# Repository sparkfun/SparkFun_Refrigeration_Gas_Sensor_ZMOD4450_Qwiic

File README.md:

SparkX Refrigeration Gas Sensor - ZMOD4450 (Qwiic)
========================================

[*SparkX Refrigeration Gas Sensor - ZMOD4450 (Qwiic) (SPX-16677)*](https://www.sparkfun.com/products/16677)

The ZMOD4450 from Renesas is a refrigeration air quality sensor designed to measure gases typically emitted during food ripening and rotting. The sensor measures ethlyene, amines and volatile sulfur compounds and reports the data via I<sup>2</sup>C. This breakout from SparkX uses the Qwiic system to easily add this sensor into your Qwiic chain. 

Feel like supporting open-source hardware? Buy a [board](https://www.sparkfun.com/products/16677) from SparkFun!

Repository Contents
-------------------

* **/Documentation** - Data sheets, additional product information
* **/Firmware** - Target Specific I<sup>2</sup>C and Low Level Functions
* **/Hardware** - Eagle design files (.brd, .sch)
* **/Production** - Production panel files (.brd)

Product Versions
----------------
* [SPX-16677](https://www.sparkfun.com/products/16677)- Original SparkX release of the Refrigeration Gas Sensor - ZMOD4450

License Information
-------------------

This product is _**open source**_! 

Please review the LICENSE.md file for license information. 

If you have any questions or concerns on licensing, please contact technical support on our [SparkFun forums](https://forum.sparkfun.com/viewforum.php?f=152).

Distributed as-is; no warranty is given.

- Your friends at SparkFun.

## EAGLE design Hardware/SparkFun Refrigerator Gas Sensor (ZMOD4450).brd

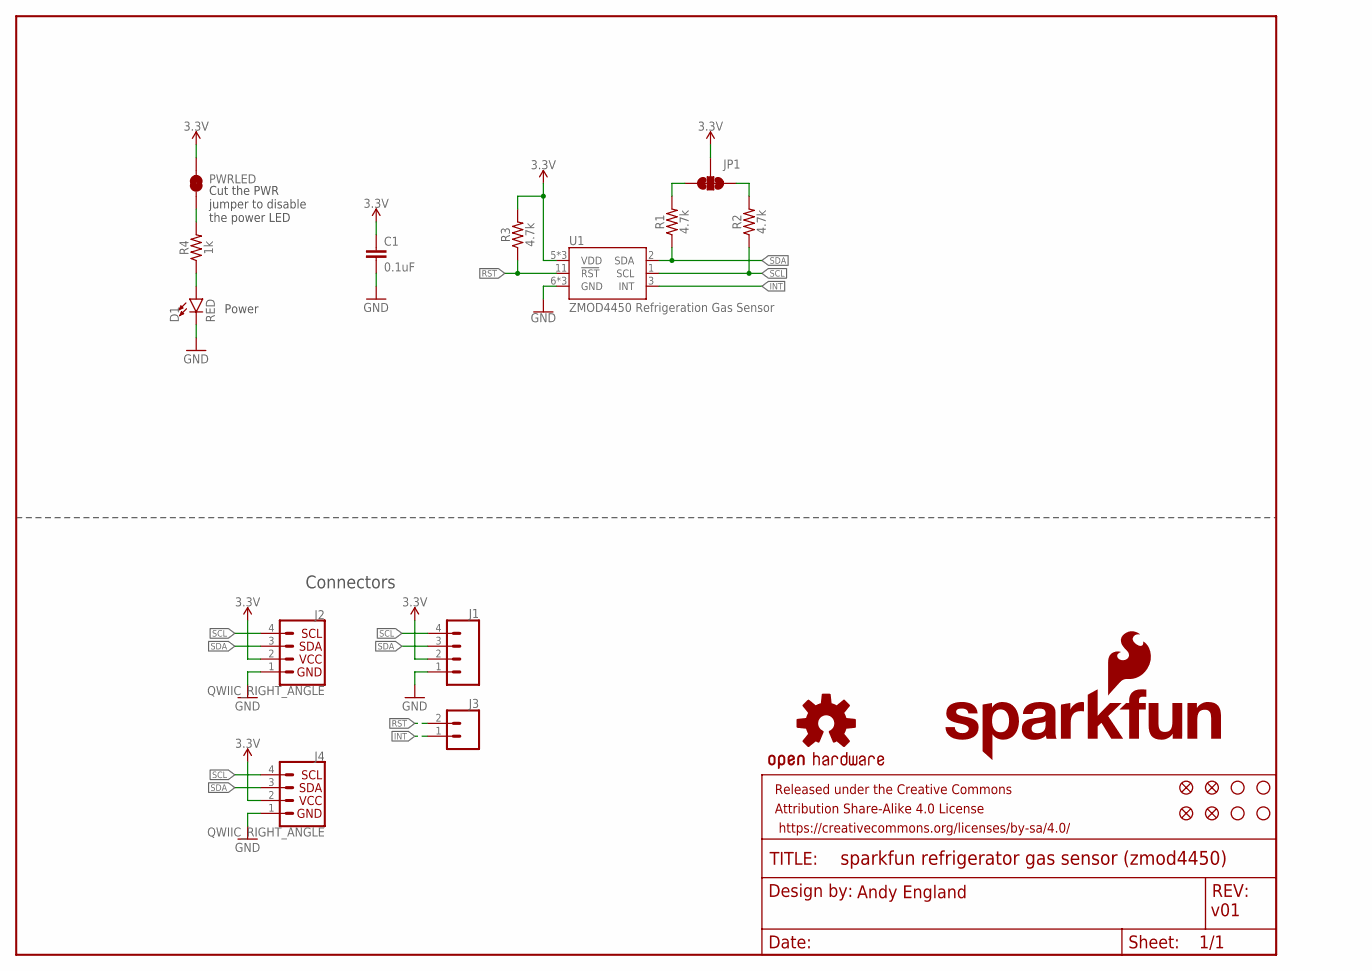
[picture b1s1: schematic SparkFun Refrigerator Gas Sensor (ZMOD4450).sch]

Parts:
C1: 0.1uF; 0603
D1: RED; LED-0603
FD1, FD2, FD3, FD4: FIDUCIALUFIDUCIAL; FIDUCIAL-MICRO
FRAME1: FRAME-LETTER; CREATIVE_COMMONS
H1, H2, H3, H4: STAND-OFF
J1: CONN_041X04_NO_SILK; 1X04_NO_SILK
J2, J4: QWIIC_RIGHT_ANGLE; JST04_1MM_RA
J3: CONN_021X02_NO_SILK; 1X02_NO_SILK
JP1: JUMPER-SMT_3_2-NC_TRACE_SILK; SMT-JUMPER_3_2-NC_TRACE_SILK
LOGO1: OSHW-LOGOS; OSHW-LOGO-S
LOGO2: SFE_LOGO_NAME_FLAME.1_INCH; SFE_LOGO_NAME_FLAME_.1
PWRLED: JUMPER-SMT_2_NC_TRACE_SILK; SMT-JUMPER_2_NC_TRACE_SILK
R1, R2, R3: 4.7k; 0603@1
R4: 1k; 0603
U1: ZMOD4450 Refrigeration Gas Sensor; LGA-12-3X3

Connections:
3.3V: C1.1, J1.2, J2.2, J4.2, JP1.2, PWRLED.2, R3.2, U1.5 (VDD), U1.10 (VDD), U1.12 (VDD); also elsewhere on the board
!RST: J3.2, R3.1, U1.11 (!RST)
GND: C1.2, D1.C, J1.1, J2.1, J4.1, U1.6 (GND), U1.7 (GND), U1.9 (GND)
INT: J3.1, U1.3 (INT)
unnamed 4: JP1.3, R1.2; also elsewhere on the board
unnamed: D1.A, R4.1
unnamed 6: JP1.1, R2.2; also elsewhere on the board
unnamed: PWRLED.1, R4.2
SCL: J1.4, J2.4, J4.4, R2.1, U1.1 (SCL)
SDA: J1.3, J2.3, J4.3, R1.1, U1.2 (SDA)

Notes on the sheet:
Andy England
v01
Power
Connectors
Cut the PWR jumper to disable the power LED

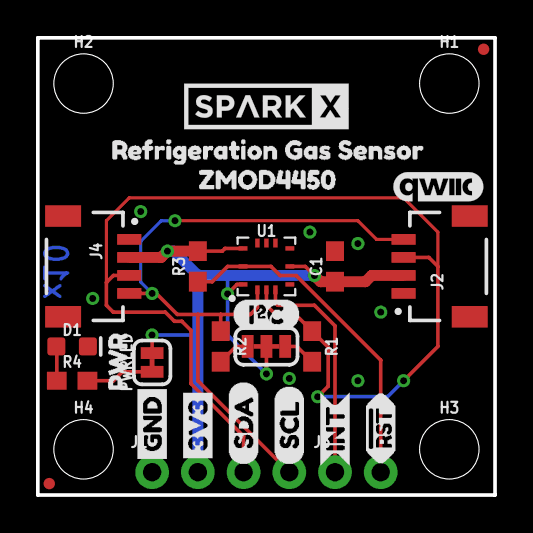
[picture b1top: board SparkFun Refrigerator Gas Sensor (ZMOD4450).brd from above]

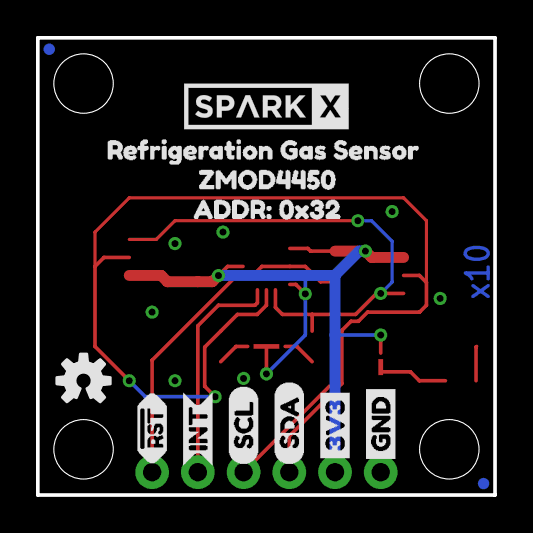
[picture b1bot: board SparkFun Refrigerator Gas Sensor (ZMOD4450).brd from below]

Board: 2 copper layers, 25.4 x 25.4 mm, 46 parts (13 on the bottom side), 10 nets.

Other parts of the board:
I2C: JUMPER-SMT_3_2-NC_TRACE_SILK; SMT-JUMPER_3_2-NC_TRACE_SILK
U$1, U$2: GND_P
U$3, U$20: ZMOD44501
U$4, U$14: INT_O
U$5, U$6: 3V3_P
U$7, U$8: SDA_IO
U$9, U$10: SCL_IO
U$11: I2C
U$12: PWR_TO
U$13, U$16: !RST_I
U$15, U$17: REFRIGERATION_GAS_SENSOR0
U$18, U$19: SPARKX-MEDIUM
U$21: ADDR#_0X320
U$22: PRODUCTION_INSTRUCTIONS

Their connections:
3.3V: I2C.2; also elsewhere on the board
unnamed 4: I2C.3; also elsewhere on the board
unnamed 6: I2C.1; also elsewhere on the board

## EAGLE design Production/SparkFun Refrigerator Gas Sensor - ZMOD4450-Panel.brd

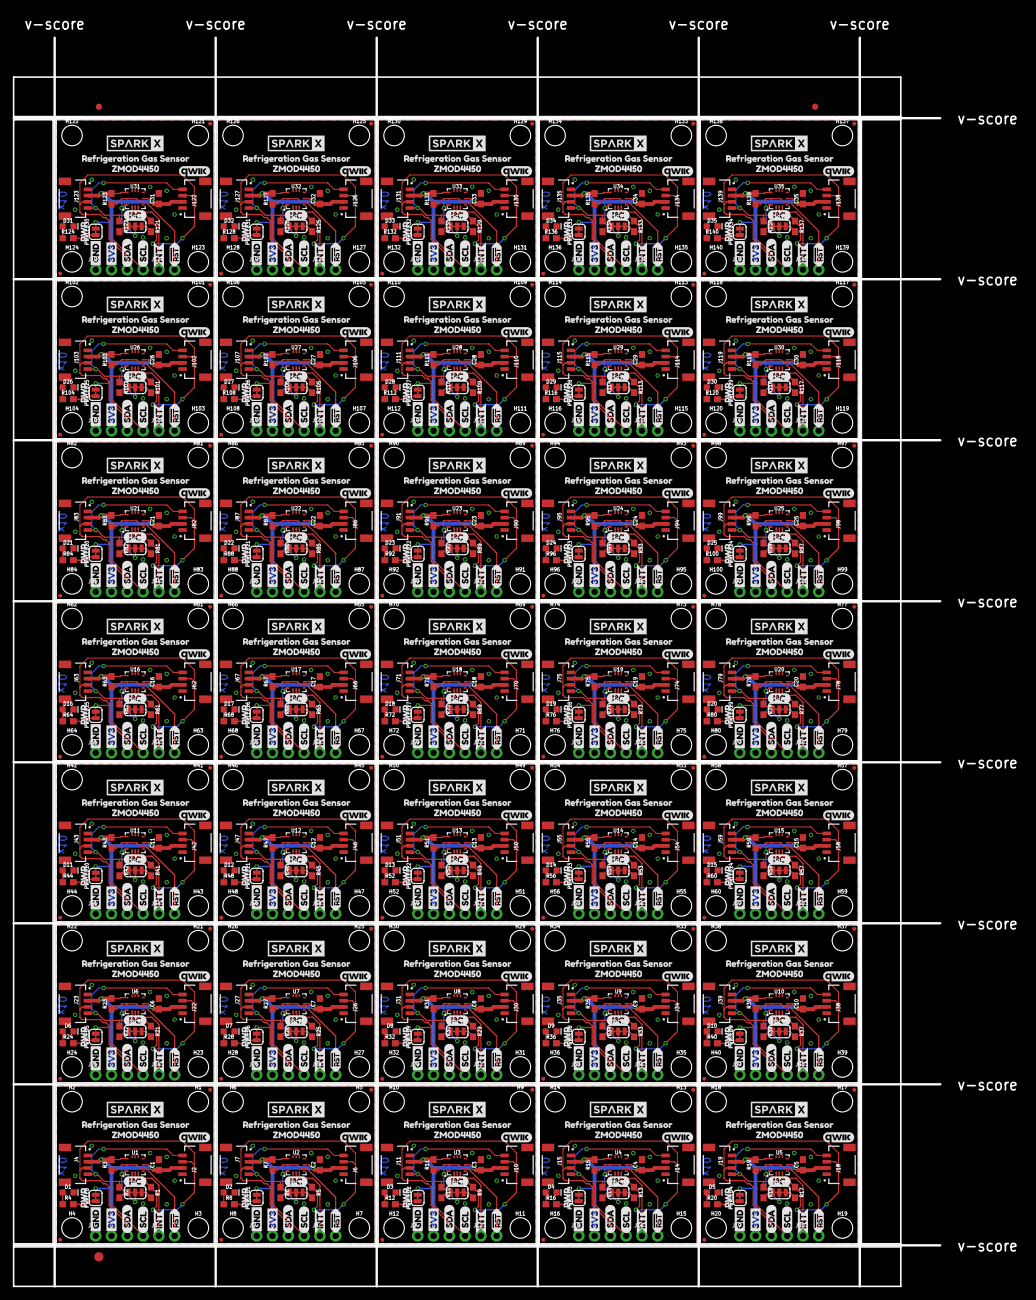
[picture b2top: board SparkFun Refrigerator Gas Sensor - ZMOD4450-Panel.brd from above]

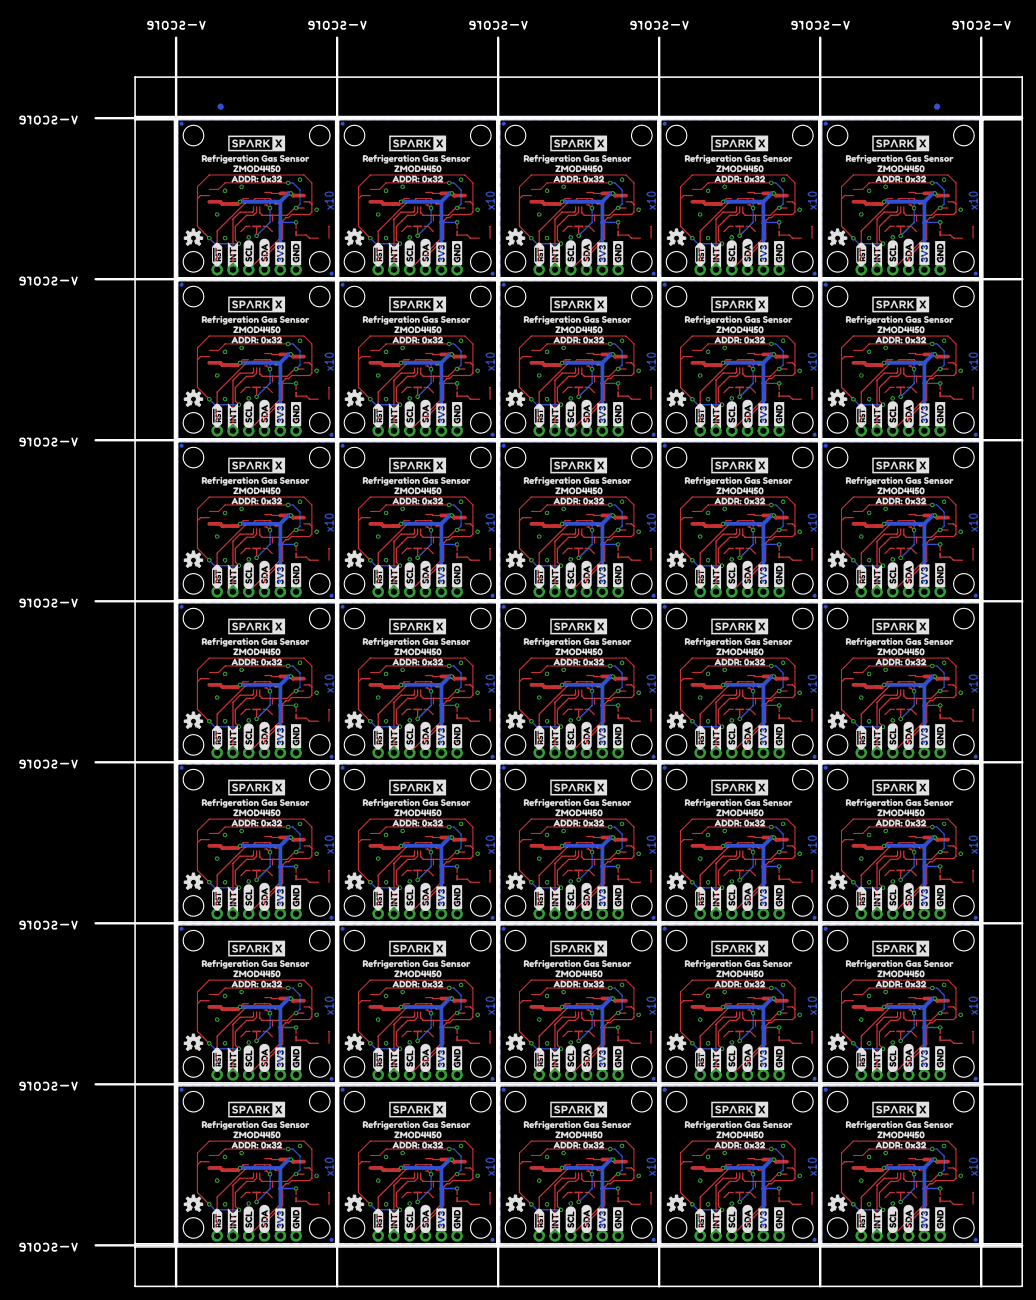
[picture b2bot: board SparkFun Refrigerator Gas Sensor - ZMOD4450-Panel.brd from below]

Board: 2 copper layers, 162.3 x 204.8 mm, 1615 parts (457 on the bottom side), 350 nets.

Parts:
C1, C2, C3, C4, C5, C6, C7, C8, C9, C10, C11, C12, C13, C14, C15, C16, C17, C18, C19, C20, C21, C22, C23, C24, C25, C26, C27, C28, C29, C30, C31, C32, C33, C34, C35: 0.1uF; 0603
D1, D2, D3, D4, D5, D6, D7, D8, D9, D10, D11, D12, D13, D14, D15, D16, D17, D18, D19, D20, D21, D22, D23, D24, D25, D26, D27, D28, D29, D30, D31, D32, D33, D34, D35: RED; LED-0603
E$1, E$2, E$3, E$4: FIDUCIAL-1X2
E$5: FIDUCIAL-1.5X3
FD1, FD2, FD3, FD4, FD5, FD6, FD7, FD8, FD9, FD10, FD11, FD12, FD13, FD14, FD15, FD16, FD17, FD18, FD19, FD20, FD21, FD22, FD23, FD24, FD25, FD26, FD27, FD28, FD29, FD30, FD31, FD32, FD33, FD34, FD35, FD36, FD37, FD38, FD39, FD40, FD41, FD42, FD43, FD44, FD45, FD46, FD47, FD48, FD49, FD50, FD51, FD52, FD53, FD54, FD55, FD56, FD57, FD58, FD59, FD60, FD61, FD62, FD63, FD64, FD65, FD66, FD67, FD68, FD69, FD70, FD71, FD72, FD73, FD74, FD75, FD76, FD77, FD78, FD79, FD80, FD81, FD82, FD83, FD84, FD85, FD86, FD87, FD88, FD89, FD90, FD91, FD92, FD93, FD94, FD95, FD96, FD97, FD98, FD99, FD100, FD101, FD102, FD103, FD104, FD105, FD106, FD107, FD108, FD109, FD110, FD111, FD112, FD113, FD114, FD115, FD116, FD117, FD118, FD119, FD120, FD121, FD122, FD123, FD124, FD125, FD126, FD127, FD128, FD129, FD130, FD131, FD132, FD133, FD134, FD135, FD136, FD137, FD138, FD139, FD140: FIDUCIALUFIDUCIAL; FIDUCIAL-MICRO
FRAME1, FRAME2, FRAME3, FRAME4, FRAME5, FRAME6, FRAME7, FRAME8, FRAME9, FRAME10, FRAME11, FRAME12, FRAME13, FRAME14, FRAME15, FRAME16, FRAME17, FRAME18, FRAME19, FRAME20, FRAME21, FRAME22, FRAME23, FRAME24, FRAME25, FRAME26, FRAME27, FRAME28, FRAME29, FRAME30, FRAME31, FRAME32, FRAME33, FRAME34, FRAME35: FRAME-LETTER; CREATIVE_COMMONS
H1, H2, H3, H4, H5, H6, H7, H8, H9, H10, H11, H12, H13, H14, H15, H16, H17, H18, H19, H20, H21, H22, H23, H24, H25, H26, H27, H28, H29, H30, H31, H32, H33, H34, H35, H36, H37, H38, H39, H40, H41, H42, H43, H44, H45, H46, H47, H48, H49, H50, H51, H52, H53, H54, H55, H56, H57, H58, H59, H60, H61, H62, H63, H64, H65, H66, H67, H68, H69, H70, H71, H72, H73, H74, H75, H76, H77, H78, H79, H80, H81, H82, H83, H84, H85, H86, H87, H88, H89, H90, H91, H92, H93, H94, H95, H96, H97, H98, H99, H100, H101, H102, H103, H104, H105, H106, H107, H108, H109, H110, H111, H112, H113, H114, H115, H116, H117, H118, H119, H120, H121, H122, H123, H124, H125, H126, H127, H128, H129, H130, H131, H132, H133, H134, H135, H136, H137, H138, H139, H140: STAND-OFF
I2C, I2C1, I2C2, I2C3, I2C4, I2C5, I2C6, I2C7, I2C8, I2C9, I2C10, I2C11, I2C12, I2C13, I2C14, I2C15, I2C16, I2C17, I2C18, I2C19, I2C20, I2C21, I2C22, I2C23, I2C24, I2C25, I2C26, I2C27, I2C28, I2C29, I2C30, I2C31, I2C32, I2C33, I2C34: JUMPER-SMT_3_2-NC_TRACE_SILK; SMT-JUMPER_3_2-NC_TRACE_SILK
J1, J5, J9, J13, J17, J21, J25, J29, J33, J37, J41, J45, J49, J53, J57, J61, J65, J69, J73, J77, J81, J85, J89, J93, J97, J101, J105, J109, J113, J117, J121, J125, J129, J133, J137: 1X04_NO_SILK
J2, J4, J6, J7, J10, J11, J14, J15, J18, J19, J22, J23, J26, J27, J30, J31, J34, J35, J38, J39, J42, J43, J46, J47, J50, J51, J54, J55, J58, J59, J62, J63, J66, J67, J70, J71, J74, J75, J78, J79, J82, J83, J86, J87, J90, J91, J94, J95, J98, J99, J102, J103, J106, J107, J110, J111, J114, J115, J118, J119, J122, J123, J126, J127, J130, J131, J134, J135, J138, J139: QWIIC_RIGHT_ANGLE; JST04_1MM_RA
J3, J8, J12, J16, J20, J24, J28, J32, J36, J40, J44, J48, J52, J56, J60, J64, J68, J72, J76, J80, J84, J88, J92, J96, J100, J104, J108, J112, J116, J120, J124, J128, J132, J136, J140: 1X02_NO_SILK
LOGO1, LOGO3, LOGO5, LOGO7, LOGO9, LOGO11, LOGO13, LOGO15, LOGO17, LOGO19, LOGO21, LOGO23, LOGO25, LOGO27, LOGO29, LOGO31, LOGO33, LOGO35, LOGO37, LOGO39, LOGO41, LOGO43, LOGO45, LOGO47, LOGO49, LOGO51, LOGO53, LOGO55, LOGO57, LOGO59, LOGO61, LOGO63, LOGO65, LOGO67, LOGO69: OSHW-LOGOS; OSHW-LOGO-S
LOGO2, LOGO4, LOGO6, LOGO8, LOGO10, LOGO12, LOGO14, LOGO16, LOGO18, LOGO20, LOGO22, LOGO24, LOGO26, LOGO28, LOGO30, LOGO32, LOGO34, LOGO36, LOGO38, LOGO40, LOGO42, LOGO44, LOGO46, LOGO48, LOGO50, LOGO52, LOGO54, LOGO56, LOGO58, LOGO60, LOGO62, LOGO64, LOGO66, LOGO68, LOGO70: QWIIC_LOGO_5MM; QWIIC_5MM
PWRLED, PWRLED1, PWRLED2, PWRLED3, PWRLED4, PWRLED5, PWRLED6, PWRLED7, PWRLED8, PWRLED9, PWRLED10, PWRLED11, PWRLED12, PWRLED13, PWRLED14, PWRLED15, PWRLED16, PWRLED17, PWRLED18, PWRLED19, PWRLED20, PWRLED21, PWRLED22, PWRLED23, PWRLED24, PWRLED25, PWRLED26, PWRLED27, PWRLED28, PWRLED29, PWRLED30, PWRLED31, PWRLED32, PWRLED33, PWRLED34: JUMPER-SMT_2_NC_TRACE_SILK; SMT-JUMPER_2_NC_TRACE_SILK
R1, R2, R3, R5, R6, R7, R9, R10, R11, R13, R14, R15, R17, R18, R19, R21, R22, R23, R25, R26, R27, R29, R30, R31, R33, R34, R35, R37, R38, R39, R41, R42, R43, R45, R46, R47, R49, R50, R51, R53, R54, R55, R57, R58, R59, R61, R62, R63, R65, R66, R67, R69, R70, R71, R73, R74, R75, R77, R78, R79, R81, R82, R83, R85, R86, R87, R89, R90, R91, R93, R94, R95, R97, R98, R99, R101, R102, R103, R105, R106, R107, R109, R110, R111, R113, R114, R115, R117, R118, R119, R121, R122, R123, R125, R126, R127, R129, R130, R131, R133, R134, R135, R137, R138, R139: 4.7k; 0603
R4, R8, R12, R16, R20, R24, R28, R32, R36, R40, R44, R48, R52, R56, R60, R64, R68, R72, R76, R80, R84, R88, R92, R96, R100, R104, R108, R112, R116, R120, R124, R128, R132, R136, R140: 1k; 0603
U1, U2, U3, U4, U5, U6, U7, U8, U9, U10, U11, U12, U13, U14, U15, U16, U17, U18, U19, U20, U21, U22, U23, U24, U25, U26, U27, U28, U29, U30, U31, U32, U33, U34, U35: ZMOD4450 Refrigeration Gas Sensor; LGA-12-3X3
U$1, U$2, U$23, U$24, U$45, U$46, U$67, U$68, U$89, U$90, U$111, U$112, U$133, U$134, U$155, U$156, U$177, U$178, U$199, U$200, U$221, U$222, U$243, U$244, U$265, U$266, U$287, U$288, U$309, U$310, U$331, U$332, U$353, U$354, U$375, U$376, U$397, U$398, U$419, U$420, U$441, U$442, U$463, U$464, U$485, U$486, U$507, U$508, U$529, U$530, U$551, U$552, U$573, U$574, U$595, U$596, U$617, U$618, U$639, U$640, U$661, U$662, U$683, U$684, U$705, U$706, U$727, U$728, U$749, U$750: GND_P
U$3, U$20, U$38, U$42, U$60, U$64, U$82, U$86, U$104, U$108, U$126, U$130, U$148, U$152, U$170, U$174, U$192, U$196, U$214, U$218, U$236, U$240, U$258, U$262, U$280, U$284, U$302, U$306, U$324, U$328, U$346, U$350, U$368, U$372, U$390, U$394, U$412, U$416, U$434, U$438, U$456, U$460, U$478, U$482, U$500, U$504, U$522, U$526, U$544, U$548, U$566, U$570, U$588, U$592, U$610, U$614, U$632, U$636, U$654, U$658, U$676, U$680, U$698, U$702, U$720, U$724, U$742, U$746, U$764, U$768: ZMOD44501
U$4, U$14, U$39, U$40, U$61, U$62, U$83, U$84, U$105, U$106, U$127, U$128, U$149, U$150, U$171, U$172, U$193, U$194, U$215, U$216, U$237, U$238, U$259, U$260, U$281, U$282, U$303, U$304, U$325, U$326, U$347, U$348, U$369, U$370, U$391, U$392, U$413, U$414, U$435, U$436, U$457, U$458, U$479, U$480, U$501, U$502, U$523, U$524, U$545, U$546, U$567, U$568, U$589, U$590, U$611, U$612, U$633, U$634, U$655, U$656, U$677, U$678, U$699, U$700, U$721, U$722, U$743, U$744, U$765, U$766: INT_O
U$5, U$6, U$25, U$26, U$47, U$48, U$69, U$70, U$91, U$92, U$113, U$114, U$135, U$136, U$157, U$158, U$179, U$180, U$201, U$202, U$223, U$224, U$245, U$246, U$267, U$268, U$289, U$290, U$311, U$312, U$333, U$334, U$355, U$356, U$377, U$378, U$399, U$400, U$421, U$422, U$443, U$444, U$465, U$466, U$487, U$488, U$509, U$510, U$531, U$532, U$553, U$554, U$575, U$576, U$597, U$598, U$619, U$620, U$641, U$642, U$663, U$664, U$685, U$686, U$707, U$708, U$729, U$730, U$751, U$752: 3V3_P
U$7, U$8, U$27, U$28, U$49, U$50, U$71, U$72, U$93, U$94, U$115, U$116, U$137, U$138, U$159, U$160, U$181, U$182, U$203, U$204, U$225, U$226, U$247, U$248, U$269, U$270, U$291, U$292, U$313, U$314, U$335, U$336, U$357, U$358, U$379, U$380, U$401, U$402, U$423, U$424, U$445, U$446, U$467, U$468, U$489, U$490, U$511, U$512, U$533, U$534, U$555, U$556, U$577, U$578, U$599, U$600, U$621, U$622, U$643, U$644, U$665, U$666, U$687, U$688, U$709, U$710, U$731, U$732, U$753, U$754: SDA_IO
U$9, U$10, U$29, U$30, U$51, U$52, U$73, U$74, U$95, U$96, U$117, U$118, U$139, U$140, U$161, U$162, U$183, U$184, U$205, U$206, U$227, U$228, U$249, U$250, U$271, U$272, U$293, U$294, U$315, U$316, U$337, U$338, U$359, U$360, U$381, U$382, U$403, U$404, U$425, U$426, U$447, U$448, U$469, U$470, U$491, U$492, U$513, U$514, U$535, U$536, U$557, U$558, U$579, U$580, U$601, U$602, U$623, U$624, U$645, U$646, U$667, U$668, U$689, U$690, U$711, U$712, U$733, U$734, U$755, U$756: SCL_IO
U$11, U$31, U$53, U$75, U$97, U$119, U$141, U$163, U$185, U$207, U$229, U$251, U$273, U$295, U$317, U$339, U$361, U$383, U$405, U$427, U$449, U$471, U$493, U$515, U$537, U$559, U$581, U$603, U$625, U$647, U$669, U$691, U$713, U$735, U$757: I2C
U$12, U$32, U$54, U$76, U$98, U$120, U$142, U$164, U$186, U$208, U$230, U$252, U$274, U$296, U$318, U$340, U$362, U$384, U$406, U$428, U$450, U$472, U$494, U$516, U$538, U$560, U$582, U$604, U$626, U$648, U$670, U$692, U$714, U$736, U$758: PWR_TO
U$13, U$16, U$33, U$34, U$55, U$56, U$77, U$78, U$99, U$100, U$121, U$122, U$143, U$144, U$165, U$166, U$187, U$188, U$209, U$210, U$231, U$232, U$253, U$254, U$275, U$276, U$297, U$298, U$319, U$320, U$341, U$342, U$363, U$364, U$385, U$386, U$407, U$408, U$429, U$430, U$451, U$452, U$473, U$474, U$495, U$496, U$517, U$518, U$539, U$540, U$561, U$562, U$583, U$584, U$605, U$606, U$627, U$628, U$649, U$650, U$671, U$672, U$693, U$694, U$715, U$716, U$737, U$738, U$759, U$760: !RST_I
U$15, U$17, U$37, U$41, U$59, U$63, U$81, U$85, U$103, U$107, U$125, U$129, U$147, U$151, U$169, U$173, U$191, U$195, U$213, U$217, U$235, U$239, U$257, U$261, U$279, U$283, U$301, U$305, U$323, U$327, U$345, U$349, U$367, U$371, U$389, U$393, U$411, U$415, U$433, U$437, U$455, U$459, U$477, U$481, U$499, U$503, U$521, U$525, U$543, U$547, U$565, U$569, U$587, U$591, U$609, U$613, U$631, U$635, U$653, U$657, U$675, U$679, U$697, U$701, U$719, U$723, U$741, U$745, U$763, U$767: REFRIGERATION_GAS_SENSOR0
U$18, U$19, U$35, U$36, U$57, U$58, U$79, U$80, U$101, U$102, U$123, U$124, U$145, U$146, U$167, U$168, U$189, U$190, U$211, U$212, U$233, U$234, U$255, U$256, U$277, U$278, U$299, U$300, U$321, U$322, U$343, U$344, U$365, U$366, U$387, U$388, U$409, U$410, U$431, U$432, U$453, U$454, U$475, U$476, U$497, U$498, U$519, U$520, U$541, U$542, U$563, U$564, U$585, U$586, U$607, U$608, U$629, U$630, U$651, U$652, U$673, U$674, U$695, U$696, U$717, U$718, U$739, U$740, U$761, U$762: SPARKX-MEDIUM
U$21, U$43, U$65, U$87, U$109, U$131, U$153, U$175, U$197, U$219, U$241, U$263, U$285, U$307, U$329, U$351, U$373, U$395, U$417, U$439, U$461, U$483, U$505, U$527, U$549, U$571, U$593, U$615, U$637, U$659, U$681, U$703, U$725, U$747, U$769: ADDR#_0X320
U$22, U$44, U$66, U$88, U$110, U$132, U$154, U$176, U$198, U$220, U$242, U$264, U$286, U$308, U$330, U$352, U$374, U$396, U$418, U$440, U$462, U$484, U$506, U$528, U$550, U$572, U$594, U$616, U$638, U$660, U$682, U$704, U$726, U$748, U$770: PRODUCTION_INSTRUCTIONS

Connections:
3.3V: C1.1, I2C.2, J1.2, J2.2, J4.2, PWRLED.2, R3.2, U1.5, U1.10, U1.12
3.3V1: C2.1, I2C1.2, J5.2, J6.2, J7.2, PWRLED1.2, R7.2, U2.5, U2.10, U2.12
3.3V2: C3.1, I2C2.2, J9.2, J10.2, J11.2, PWRLED2.2, R11.2, U3.5, U3.10, U3.12
3.3V3: C4.1, I2C3.2, J13.2, J14.2, J15.2, PWRLED3.2, R15.2, U4.5, U4.10, U4.12
3.3V4: C5.1, I2C4.2, J17.2, J18.2, J19.2, PWRLED4.2, R19.2, U5.5, U5.10, U5.12
3.3V5: C6.1, I2C5.2, J21.2, J22.2, J23.2, PWRLED5.2, R23.2, U6.5, U6.10, U6.12
3.3V6: C7.1, I2C6.2, J25.2, J26.2, J27.2, PWRLED6.2, R27.2, U7.5, U7.10, U7.12
3.3V7: C8.1, I2C7.2, J29.2, J30.2, J31.2, PWRLED7.2, R31.2, U8.5, U8.10, U8.12
3.3V8: C9.1, I2C8.2, J33.2, J34.2, J35.2, PWRLED8.2, R35.2, U9.5, U9.10, U9.12
3.3V9: C10.1, I2C9.2, J37.2, J38.2, J39.2, PWRLED9.2, R39.2, U10.5, U10.10, U10.12
3.3V10: C11.1, I2C10.2, J41.2, J42.2, J43.2, PWRLED10.2, R43.2, U11.5, U11.10, U11.12
3.3V11: C12.1, I2C11.2, J45.2, J46.2, J47.2, PWRLED11.2, R47.2, U12.5, U12.10, U12.12
3.3V12: C13.1, I2C12.2, J49.2, J50.2, J51.2, PWRLED12.2, R51.2, U13.5, U13.10, U13.12
3.3V13: C14.1, I2C13.2, J53.2, J54.2, J55.2, PWRLED13.2, R55.2, U14.5, U14.10, U14.12
3.3V14: C15.1, I2C14.2, J57.2, J58.2, J59.2, PWRLED14.2, R59.2, U15.5, U15.10, U15.12
3.3V15: C16.1, I2C15.2, J61.2, J62.2, J63.2, PWRLED15.2, R63.2, U16.5, U16.10, U16.12
3.3V16: C17.1, I2C16.2, J65.2, J66.2, J67.2, PWRLED16.2, R67.2, U17.5, U17.10, U17.12
3.3V17: C18.1, I2C17.2, J69.2, J70.2, J71.2, PWRLED17.2, R71.2, U18.5, U18.10, U18.12
3.3V18: C19.1, I2C18.2, J73.2, J74.2, J75.2, PWRLED18.2, R75.2, U19.5, U19.10, U19.12
3.3V19: C20.1, I2C19.2, J77.2, J78.2, J79.2, PWRLED19.2, R79.2, U20.5, U20.10, U20.12
3.3V20: C21.1, I2C20.2, J81.2, J82.2, J83.2, PWRLED20.2, R83.2, U21.5, U21.10, U21.12
3.3V21: C22.1, I2C21.2, J85.2, J86.2, J87.2, PWRLED21.2, R87.2, U22.5, U22.10, U22.12
3.3V22: C23.1, I2C22.2, J89.2, J90.2, J91.2, PWRLED22.2, R91.2, U23.5, U23.10, U23.12
3.3V23: C24.1, I2C23.2, J93.2, J94.2, J95.2, PWRLED23.2, R95.2, U24.5, U24.10, U24.12
3.3V24: C25.1, I2C24.2, J97.2, J98.2, J99.2, PWRLED24.2, R99.2, U25.5, U25.10, U25.12
3.3V25: C26.1, I2C25.2, J101.2, J102.2, J103.2, PWRLED25.2, R103.2, U26.5, U26.10, U26.12
3.3V26: C27.1, I2C26.2, J105.2, J106.2, J107.2, PWRLED26.2, R107.2, U27.5, U27.10, U27.12
3.3V27: C28.1, I2C27.2, J109.2, J110.2, J111.2, PWRLED27.2, R111.2, U28.5, U28.10, U28.12
3.3V28: C29.1, I2C28.2, J113.2, J114.2, J115.2, PWRLED28.2, R115.2, U29.5, U29.10, U29.12
3.3V29: C30.1, I2C29.2, J117.2, J118.2, J119.2, PWRLED29.2, R119.2, U30.5, U30.10, U30.12
3.3V30: C31.1, I2C30.2, J121.2, J122.2, J123.2, PWRLED30.2, R123.2, U31.5, U31.10, U31.12
3.3V31: C32.1, I2C31.2, J125.2, J126.2, J127.2, PWRLED31.2, R127.2, U32.5, U32.10, U32.12
3.3V32: C33.1, I2C32.2, J129.2, J130.2, J131.2, PWRLED32.2, R131.2, U33.5, U33.10, U33.12
3.3V33: C34.1, I2C33.2, J133.2, J134.2, J135.2, PWRLED33.2, R135.2, U34.5, U34.10, U34.12
3.3V34: C35.1, I2C34.2, J137.2, J138.2, J139.2, PWRLED34.2, R139.2, U35.5, U35.10, U35.12
!RST: J3.2, R3.1, U1.11
!RST1: J8.2, R7.1, U2.11
!RST2: J12.2, R11.1, U3.11
!RST3: J16.2, R15.1, U4.11
!RST4: J20.2, R19.1, U5.11
!RST5: J24.2, R23.1, U6.11
!RST6: J28.2, R27.1, U7.11
!RST7: J32.2, R31.1, U8.11
!RST8: J36.2, R35.1, U9.11
!RST9: J40.2, R39.1, U10.11
!RST10: J44.2, R43.1, U11.11
!RST11: J48.2, R47.1, U12.11
!RST12: J52.2, R51.1, U13.11
!RST13: J56.2, R55.1, U14.11
!RST14: J60.2, R59.1, U15.11
!RST15: J64.2, R63.1, U16.11
!RST16: J68.2, R67.1, U17.11
!RST17: J72.2, R71.1, U18.11
!RST18: J76.2, R75.1, U19.11
!RST19: J80.2, R79.1, U20.11
!RST20: J84.2, R83.1, U21.11
!RST21: J88.2, R87.1, U22.11
!RST22: J92.2, R91.1, U23.11
!RST23: J96.2, R95.1, U24.11
!RST24: J100.2, R99.1, U25.11
!RST25: J104.2, R103.1, U26.11
!RST26: J108.2, R107.1, U27.11
!RST27: J112.2, R111.1, U28.11
!RST28: J116.2, R115.1, U29.11
!RST29: J120.2, R119.1, U30.11
!RST30: J124.2, R123.1, U31.11
!RST31: J128.2, R127.1, U32.11
!RST32: J132.2, R131.1, U33.11
!RST33: J136.2, R135.1, U34.11
!RST34: J140.2, R139.1, U35.11
GND: C1.2, D1.C, J1.1, J2.1, J4.1, U1.6, U1.7, U1.9
GND1: C2.2, D2.C, J5.1, J6.1, J7.1, U2.6, U2.7, U2.9
GND2: C3.2, D3.C, J9.1, J10.1, J11.1, U3.6, U3.7, U3.9
GND3: C4.2, D4.C, J13.1, J14.1, J15.1, U4.6, U4.7, U4.9
GND4: C5.2, D5.C, J17.1, J18.1, J19.1, U5.6, U5.7, U5.9
GND5: C6.2, D6.C, J21.1, J22.1, J23.1, U6.6, U6.7, U6.9
GND6: C7.2, D7.C, J25.1, J26.1, J27.1, U7.6, U7.7, U7.9
GND7: C8.2, D8.C, J29.1, J30.1, J31.1, U8.6, U8.7, U8.9
GND8: C9.2, D9.C, J33.1, J34.1, J35.1, U9.6, U9.7, U9.9
GND9: C10.2, D10.C, J37.1, J38.1, J39.1, U10.6, U10.7, U10.9
GND10: C11.2, D11.C, J41.1, J42.1, J43.1, U11.6, U11.7, U11.9
GND11: C12.2, D12.C, J45.1, J46.1, J47.1, U12.6, U12.7, U12.9
GND12: C13.2, D13.C, J49.1, J50.1, J51.1, U13.6, U13.7, U13.9
GND13: C14.2, D14.C, J53.1, J54.1, J55.1, U14.6, U14.7, U14.9
GND14: C15.2, D15.C, J57.1, J58.1, J59.1, U15.6, U15.7, U15.9
GND15: C16.2, D16.C, J61.1, J62.1, J63.1, U16.6, U16.7, U16.9
GND16: C17.2, D17.C, J65.1, J66.1, J67.1, U17.6, U17.7, U17.9
GND17: C18.2, D18.C, J69.1, J70.1, J71.1, U18.6, U18.7, U18.9
GND18: C19.2, D19.C, J73.1, J74.1, J75.1, U19.6, U19.7, U19.9
GND19: C20.2, D20.C, J77.1, J78.1, J79.1, U20.6, U20.7, U20.9
GND20: C21.2, D21.C, J81.1, J82.1, J83.1, U21.6, U21.7, U21.9
GND21: C22.2, D22.C, J85.1, J86.1, J87.1, U22.6, U22.7, U22.9
GND22: C23.2, D23.C, J89.1, J90.1, J91.1, U23.6, U23.7, U23.9
GND23: C24.2, D24.C, J93.1, J94.1, J95.1, U24.6, U24.7, U24.9
GND24: C25.2, D25.C, J97.1, J98.1, J99.1, U25.6, U25.7, U25.9
GND25: C26.2, D26.C, J101.1, J102.1, J103.1, U26.6, U26.7, U26.9
GND26: C27.2, D27.C, J105.1, J106.1, J107.1, U27.6, U27.7, U27.9
GND27: C28.2, D28.C, J109.1, J110.1, J111.1, U28.6, U28.7, U28.9
GND28: C29.2, D29.C, J113.1, J114.1, J115.1, U29.6, U29.7, U29.9
GND29: C30.2, D30.C, J117.1, J118.1, J119.1, U30.6, U30.7, U30.9
GND30: C31.2, D31.C, J121.1, J122.1, J123.1, U31.6, U31.7, U31.9
GND31: C32.2, D32.C, J125.1, J126.1, J127.1, U32.6, U32.7, U32.9
GND32: C33.2, D33.C, J129.1, J130.1, J131.1, U33.6, U33.7, U33.9
GND33: C34.2, D34.C, J133.1, J134.1, J135.1, U34.6, U34.7, U34.9
GND34: C35.2, D35.C, J137.1, J138.1, J139.1, U35.6, U35.7, U35.9
INT: J3.1, U1.3
INT1: J8.1, U2.3
INT2: J12.1, U3.3
INT3: J16.1, U4.3
INT4: J20.1, U5.3
INT5: J24.1, U6.3
INT6: J28.1, U7.3
INT7: J32.1, U8.3
INT8: J36.1, U9.3
INT9: J40.1, U10.3
INT10: J44.1, U11.3
INT11: J48.1, U12.3
INT12: J52.1, U13.3
INT13: J56.1, U14.3
INT14: J60.1, U15.3
INT15: J64.1, U16.3
INT16: J68.1, U17.3
INT17: J72.1, U18.3
INT18: J76.1, U19.3
INT19: J80.1, U20.3
INT20: J84.1, U21.3
INT21: J88.1, U22.3
INT22: J92.1, U23.3
INT23: J96.1, U24.3
INT24: J100.1, U25.3
INT25: J104.1, U26.3
INT26: J108.1, U27.3
INT27: J112.1, U28.3
INT28: J116.1, U29.3
INT29: J120.1, U30.3
INT30: J124.1, U31.3
INT31: J128.1, U32.3
INT32: J132.1, U33.3
INT33: J136.1, U34.3
INT34: J140.1, U35.3
unnamed: I2C.3, R1.2
unnamed: D1.A, R4.1
unnamed: I2C.1, R2.2
unnamed: PWRLED.1, R4.2
unnamed: I2C1.3, R5.2
unnamed: I2C1.1, R6.2
unnamed: D2.A, R8.1
unnamed: PWRLED1.1, R8.2
unnamed: I2C2.3, R9.2
unnamed: I2C2.1, R10.2
unnamed: D3.A, R12.1
unnamed: PWRLED2.1, R12.2
unnamed: I2C3.3, R13.2
unnamed: I2C3.1, R14.2
unnamed: D4.A, R16.1
unnamed: PWRLED3.1, R16.2
unnamed: I2C4.3, R17.2
unnamed: I2C4.1, R18.2
unnamed: D5.A, R20.1
unnamed: PWRLED4.1, R20.2
unnamed: I2C5.3, R21.2
unnamed: I2C5.1, R22.2
unnamed: D6.A, R24.1
unnamed: PWRLED5.1, R24.2
unnamed: I2C6.3, R25.2
unnamed: I2C6.1, R26.2
unnamed: D7.A, R28.1
unnamed: PWRLED6.1, R28.2
unnamed: I2C7.3, R29.2
unnamed: I2C7.1, R30.2
unnamed: D8.A, R32.1
unnamed: PWRLED7.1, R32.2
unnamed: I2C8.3, R33.2
unnamed: I2C8.1, R34.2
unnamed: D9.A, R36.1
unnamed: PWRLED8.1, R36.2
unnamed: I2C9.3, R37.2
unnamed: I2C9.1, R38.2
unnamed: D10.A, R40.1
unnamed: PWRLED9.1, R40.2
unnamed: I2C10.3, R41.2
unnamed: I2C10.1, R42.2
unnamed: D11.A, R44.1
unnamed: PWRLED10.1, R44.2
unnamed: I2C11.3, R45.2
unnamed: I2C11.1, R46.2
unnamed: D12.A, R48.1
unnamed: PWRLED11.1, R48.2
unnamed: I2C12.3, R49.2
unnamed: I2C12.1, R50.2
unnamed: D13.A, R52.1
unnamed: PWRLED12.1, R52.2
unnamed: I2C13.3, R53.2
unnamed: I2C13.1, R54.2
unnamed: D14.A, R56.1
unnamed: PWRLED13.1, R56.2
unnamed: I2C14.3, R57.2
unnamed: I2C14.1, R58.2
unnamed: D15.A, R60.1
unnamed: PWRLED14.1, R60.2
unnamed: I2C15.3, R61.2
unnamed: I2C15.1, R62.2
unnamed: D16.A, R64.1
unnamed: PWRLED15.1, R64.2
unnamed: I2C16.3, R65.2
unnamed: I2C16.1, R66.2
unnamed: D17.A, R68.1
unnamed: PWRLED16.1, R68.2
unnamed: I2C17.3, R69.2
unnamed: I2C17.1, R70.2
unnamed: D18.A, R72.1
unnamed: PWRLED17.1, R72.2
unnamed: I2C18.3, R73.2
unnamed: I2C18.1, R74.2
unnamed: D19.A, R76.1
unnamed: PWRLED18.1, R76.2
unnamed: I2C19.3, R77.2
unnamed: I2C19.1, R78.2
unnamed: D20.A, R80.1
unnamed: PWRLED19.1, R80.2
unnamed: I2C20.3, R81.2
unnamed: I2C20.1, R82.2
unnamed: D21.A, R84.1
unnamed: PWRLED20.1, R84.2
unnamed: I2C21.3, R85.2
unnamed: I2C21.1, R86.2
unnamed: D22.A, R88.1
unnamed: PWRLED21.1, R88.2
unnamed: I2C22.3, R89.2
unnamed: I2C22.1, R90.2
unnamed: D23.A, R92.1
unnamed: PWRLED22.1, R92.2
unnamed: I2C23.3, R93.2
unnamed: I2C23.1, R94.2
unnamed: D24.A, R96.1
unnamed: PWRLED23.1, R96.2
unnamed: I2C24.3, R97.2
unnamed: I2C24.1, R98.2
unnamed: D25.A, R100.1
unnamed: PWRLED24.1, R100.2
unnamed: I2C25.3, R101.2
unnamed: I2C25.1, R102.2
unnamed: D26.A, R104.1
unnamed: PWRLED25.1, R104.2
unnamed: I2C26.3, R105.2
unnamed: I2C26.1, R106.2
unnamed: D27.A, R108.1
unnamed: PWRLED26.1, R108.2
unnamed: I2C27.3, R109.2
unnamed: I2C27.1, R110.2
unnamed: D28.A, R112.1
unnamed: PWRLED27.1, R112.2
unnamed: I2C28.3, R113.2
unnamed: I2C28.1, R114.2
unnamed: D29.A, R116.1
unnamed: PWRLED28.1, R116.2
unnamed: I2C29.3, R117.2
unnamed: I2C29.1, R118.2
unnamed: D30.A, R120.1
unnamed: PWRLED29.1, R120.2
unnamed: I2C30.3, R121.2
unnamed: I2C30.1, R122.2
unnamed: D31.A, R124.1
unnamed: PWRLED30.1, R124.2
unnamed: I2C31.3, R125.2
unnamed: I2C31.1, R126.2
unnamed: D32.A, R128.1
unnamed: PWRLED31.1, R128.2
unnamed: I2C32.3, R129.2
unnamed: I2C32.1, R130.2
unnamed: D33.A, R132.1
unnamed: PWRLED32.1, R132.2
unnamed: I2C33.3, R133.2
unnamed: I2C33.1, R134.2
unnamed: D34.A, R136.1
unnamed: PWRLED33.1, R136.2
unnamed: I2C34.3, R137.2
unnamed: I2C34.1, R138.2
unnamed: D35.A, R140.1
unnamed: PWRLED34.1, R140.2
SCL: J1.4, J2.4, J4.4, R2.1, U1.1
SCL1: J5.4, J6.4, J7.4, R6.1, U2.1
SCL2: J9.4, J10.4, J11.4, R10.1, U3.1
SCL3: J13.4, J14.4, J15.4, R14.1, U4.1
SCL4: J17.4, J18.4, J19.4, R18.1, U5.1
SCL5: J21.4, J22.4, J23.4, R22.1, U6.1
SCL6: J25.4, J26.4, J27.4, R26.1, U7.1
SCL7: J29.4, J30.4, J31.4, R30.1, U8.1
SCL8: J33.4, J34.4, J35.4, R34.1, U9.1
SCL9: J37.4, J38.4, J39.4, R38.1, U10.1
SCL10: J41.4, J42.4, J43.4, R42.1, U11.1
SCL11: J45.4, J46.4, J47.4, R46.1, U12.1
SCL12: J49.4, J50.4, J51.4, R50.1, U13.1
SCL13: J53.4, J54.4, J55.4, R54.1, U14.1
SCL14: J57.4, J58.4, J59.4, R58.1, U15.1
SCL15: J61.4, J62.4, J63.4, R62.1, U16.1
SCL16: J65.4, J66.4, J67.4, R66.1, U17.1
SCL17: J69.4, J70.4, J71.4, R70.1, U18.1
SCL18: J73.4, J74.4, J75.4, R74.1, U19.1
SCL19: J77.4, J78.4, J79.4, R78.1, U20.1
SCL20: J81.4, J82.4, J83.4, R82.1, U21.1
SCL21: J85.4, J86.4, J87.4, R86.1, U22.1
SCL22: J89.4, J90.4, J91.4, R90.1, U23.1
SCL23: J93.4, J94.4, J95.4, R94.1, U24.1
SCL24: J97.4, J98.4, J99.4, R98.1, U25.1
SCL25: J101.4, J102.4, J103.4, R102.1, U26.1
SCL26: J105.4, J106.4, J107.4, R106.1, U27.1
SCL27: J109.4, J110.4, J111.4, R110.1, U28.1
SCL28: J113.4, J114.4, J115.4, R114.1, U29.1
SCL29: J117.4, J118.4, J119.4, R118.1, U30.1
SCL30: J121.4, J122.4, J123.4, R122.1, U31.1
SCL31: J125.4, J126.4, J127.4, R126.1, U32.1
SCL32: J129.4, J130.4, J131.4, R130.1, U33.1
SCL33: J133.4, J134.4, J135.4, R134.1, U34.1
SCL34: J137.4, J138.4, J139.4, R138.1, U35.1
SDA: J1.3, J2.3, J4.3, R1.1, U1.2
SDA1: J5.3, J6.3, J7.3, R5.1, U2.2
SDA2: J9.3, J10.3, J11.3, R9.1, U3.2
SDA3: J13.3, J14.3, J15.3, R13.1, U4.2
SDA4: J17.3, J18.3, J19.3, R17.1, U5.2
SDA5: J21.3, J22.3, J23.3, R21.1, U6.2
SDA6: J25.3, J26.3, J27.3, R25.1, U7.2
SDA7: J29.3, J30.3, J31.3, R29.1, U8.2
SDA8: J33.3, J34.3, J35.3, R33.1, U9.2
SDA9: J37.3, J38.3, J39.3, R37.1, U10.2
SDA10: J41.3, J42.3, J43.3, R41.1, U11.2
SDA11: J45.3, J46.3, J47.3, R45.1, U12.2
SDA12: J49.3, J50.3, J51.3, R49.1, U13.2
SDA13: J53.3, J54.3, J55.3, R53.1, U14.2
SDA14: J57.3, J58.3, J59.3, R57.1, U15.2
SDA15: J61.3, J62.3, J63.3, R61.1, U16.2
SDA16: J65.3, J66.3, J67.3, R65.1, U17.2
SDA17: J69.3, J70.3, J71.3, R69.1, U18.2
SDA18: J73.3, J74.3, J75.3, R73.1, U19.2
SDA19: J77.3, J78.3, J79.3, R77.1, U20.2
SDA20: J81.3, J82.3, J83.3, R81.1, U21.2
SDA21: J85.3, J86.3, J87.3, R85.1, U22.2
SDA22: J89.3, J90.3, J91.3, R89.1, U23.2
SDA23: J93.3, J94.3, J95.3, R93.1, U24.2
SDA24: J97.3, J98.3, J99.3, R97.1, U25.2
SDA25: J101.3, J102.3, J103.3, R101.1, U26.2
SDA26: J105.3, J106.3, J107.3, R105.1, U27.2
SDA27: J109.3, J110.3, J111.3, R109.1, U28.2
SDA28: J113.3, J114.3, J115.3, R113.1, U29.2
SDA29: J117.3, J118.3, J119.3, R117.1, U30.2
SDA30: J121.3, J122.3, J123.3, R121.1, U31.2
SDA31: J125.3, J126.3, J127.3, R125.1, U32.2
SDA32: J129.3, J130.3, J131.3, R129.1, U33.2
SDA33: J133.3, J134.3, J135.3, R133.1, U34.2
SDA34: J137.3, J138.3, J139.3, R137.1, U35.2

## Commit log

2020-04-27 initial commit/layout
2020-05-06 Checklist changes
2020-05-06 Changing INT silk
2020-05-08 adding initial panel
2020-05-12 adding datasheet
2020-06-08 cleaning up for launch
2020-06-08 adding firmware zip
2020-06-11 Updating README
    Adding product photos and updating description and links.

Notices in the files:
parts and their libraries:
SparkFun-Capacitors: Licensing: Creative Commons ShareAlike 4.0 International - https://creativecommons.org/licenses/by-sa/4.0
SparkFun-Aesthetics: Released under the Creative Commons Attribution Share-Alike 4.0 License
SparkFun-Aesthetics: https://creativecommons.org/licenses/by-sa/4.0
